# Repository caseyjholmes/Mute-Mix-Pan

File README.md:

# Mute-Mix-Pan

NOTE:
this is an outdated version of my mixer. use the new MMPV3 repository files

5 Channel Mono Mutable Mixer with Pan output for Eurorack

A simple knob controlled 5 channel mono eurorack mixer with mute switches, master volume and panning balance outputs. 
Component values are printed on the board. Minimum component size is 0805.

Install switches first, then front panel. The switches are "tall". Solder in jacks to the right height after the switches are in place. Finally, you can solder in the potentiometers. 

Panel has been added now.

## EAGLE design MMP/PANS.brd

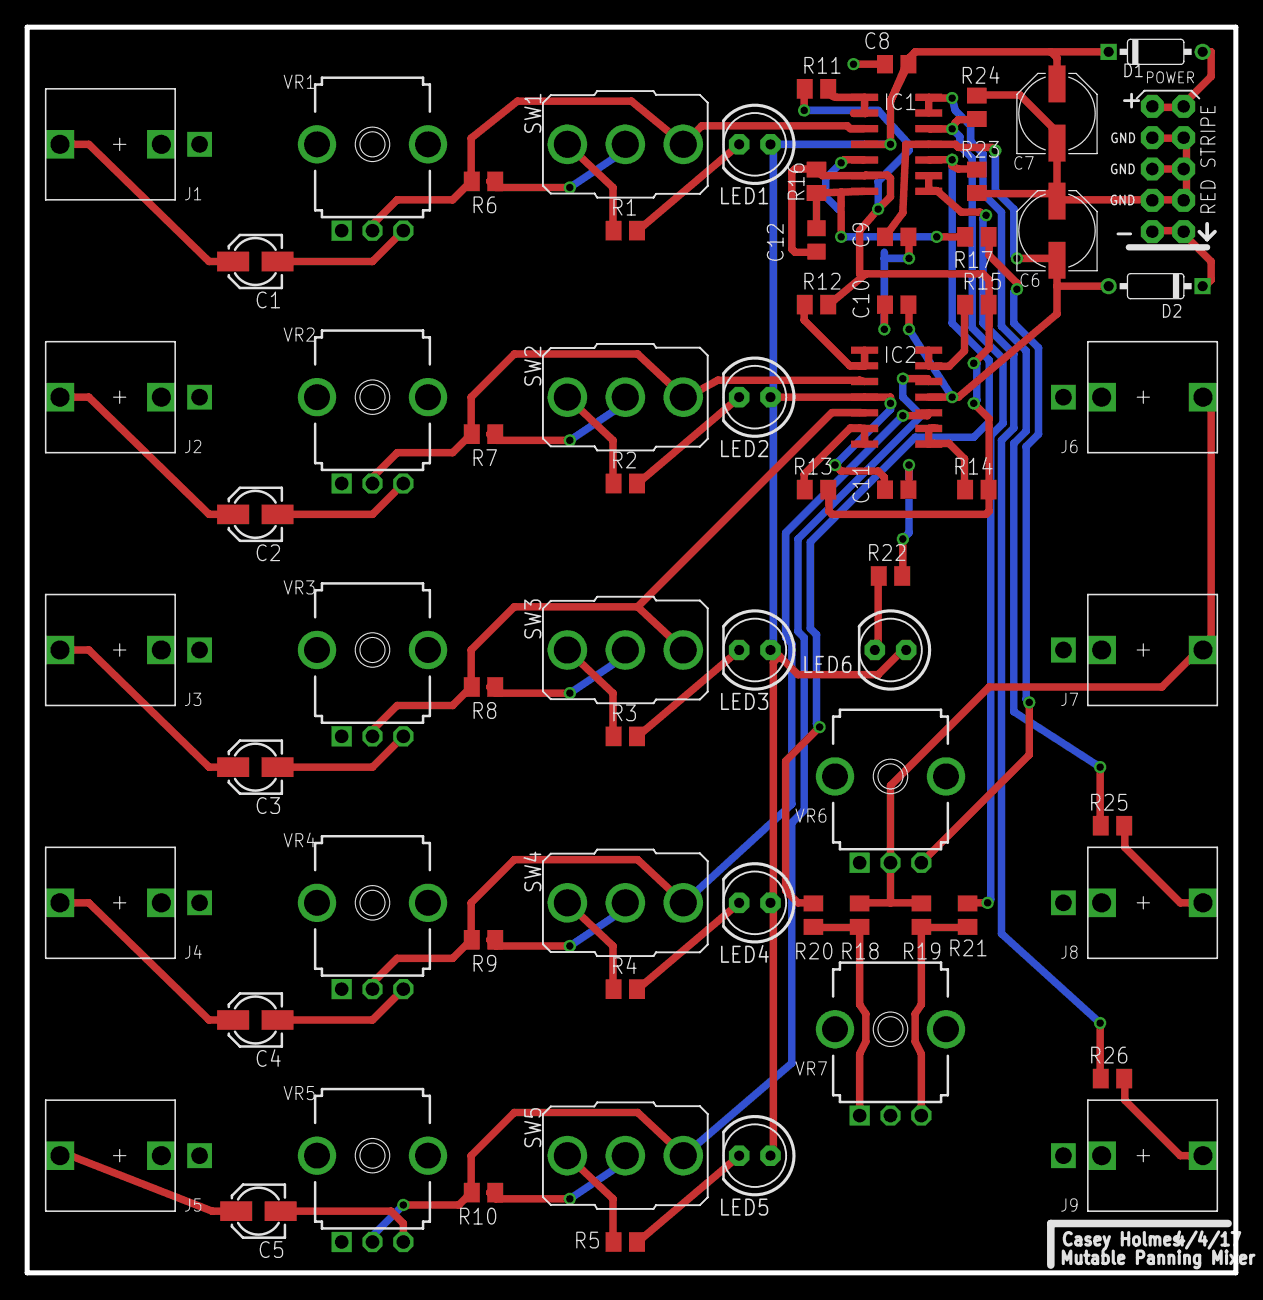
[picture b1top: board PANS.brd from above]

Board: 2 copper layers, 98.0 x 101.0 mm, 70 parts (0 on the bottom side), 48 nets.

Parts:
C1, C2, C3, C4, C5: 10uf; 153CLV-0405
C6, C7: 47uf; PANASONIC_D
C8, C9, C10, C11: 100n; C0805
C12: XXX; C0805
D1, D2: 1N5817; DO35-7
IC1, IC2: TL074; SO14
J1, J2, J3, J4, J5, J6, J7, J8, J9: THONKICONNOLD; THONKICONN
LED1, LED2, LED3, LED4, LED5, LED6: green; LED5MM
R1, R2, R3, R4, R5, R17, R18, R19, R20, R21, R25, R26: 1K; M0805
R6, R7, R8, R9, R10, R11, R12, R13, R14, R15, R16, R22, R23, R24: 100K; M0805
SV1: SV1; EURO_PWR_HEADER_FAT
SW1, SW2, SW3, SW4, SW5: on/on; M9040P
VR1, VR2, VR3, VR4, VR5: 1M; 9MM_SNAP-IN_POT
VR6, VR7: 10K; 9MM_SNAP-IN_POT

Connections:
GND: C6.+, C7.-, C8.1, C9.1, C10.1, C11.2, IC1.5, J1.P$1_SLEEVE, J2.P$1_SLEEVE, J3.P$1_SLEEVE, J4.P$1_SLEEVE, J5.P$1_SLEEVE, J6.P$1_SLEEVE, J7.P$1_SLEEVE, J8.P$1_SLEEVE, J9.P$1_SLEEVE, R6.1, R7.1, R8.1, R9.1, R10.1, R22.2, R23.1, R24.2, SV1.3, SV1.4, SV1.5, SV1.6, SV1.7, SV1.8, SW1.2, SW2.2, SW3.2, SW4.2, SW5.2, VR1.1, VR2.1, VR3.1, VR4.1, VR5.1, VR6.1, VR7.2
S$1: C1.+, J1.P$3_TIP
S$2: C2.+, J2.P$3_TIP
S$3: C3.+, J3.P$3_TIP
S$4: C4.+, J4.P$3_TIP
S$5: C5.+, J5.P$3_TIP
S$6: C1.-, VR1.3
S$7: C2.-, VR2.3
S$8: C3.-, VR3.3
S$9: C4.-, VR4.3
S$10: C5.-, VR5.3
S$11: IC1.3, R6.2, SW1.3, VR1.2
S$12: IC2.3, R7.2, SW2.3, VR2.2
S$13: IC2.5, R8.2, SW3.3, VR3.2
S$14: IC2.10, R9.2, SW4.3, VR4.2
S$15: IC2.12, R10.2, SW5.3, VR5.2
S$16: D1.A, SV1.9, SV1.10
S$17: D2.C, SV1.1, SV1.2
S$18: LED5.K, R5.2
S$19: J6.P$3_TIP, J7.P$3_TIP, R18.2, R19.2, VR6.2
S$20: R18.1, R20.1, VR7.1
S$21: R19.1, R21.1, VR7.3
S$22: IC1.10, R20.2, R23.2
S$23: IC2.13, IC2.14, R15.1
S$24: IC1.8, IC1.9, R26.2
S$25: LED6.K, R22.1
S$26: R1.1, SW1.1
S$27: R2.1, SW2.1
S$28: R3.1, SW3.1
S$29: R4.1, SW4.1
S$30: R5.1, SW5.1
S$31: LED4.K, R4.2
S$34: IC1.13, IC1.14, R25.2
S$35: J8.P$3_TIP, R25.1
S$36: IC1.12, R21.2, R24.1
S$37: LED3.K, R3.2
S$38: LED2.K, R2.2
S$39: LED1.K, R1.2
S$41: J9.P$3_TIP, R26.1
S$42: IC2.1, IC2.2, R12.1
S$43: IC2.6, IC2.7, R13.1
S$45: IC2.8, IC2.9, R14.1
S$46: IC1.1, IC1.2, R11.2
S$47: R17.2, VR6.3
S$48: C6.-, C9.2, C10.2, D2.A, IC1.11, IC2.11
S$50: C12.2, IC1.6, R11.1, R12.2, R13.2, R14.2, R15.2, R16.2
S$51: C12.1, IC1.7, R16.1, R17.1
V+: C7.+, C8.2, C11.1, D1.C, IC1.4, IC2.4, LED1.A, LED2.A, LED3.A, LED4.A, LED5.A, LED6.A
